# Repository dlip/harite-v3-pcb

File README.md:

# Harite v3.0 PCB

[Build Guide](/build.md)

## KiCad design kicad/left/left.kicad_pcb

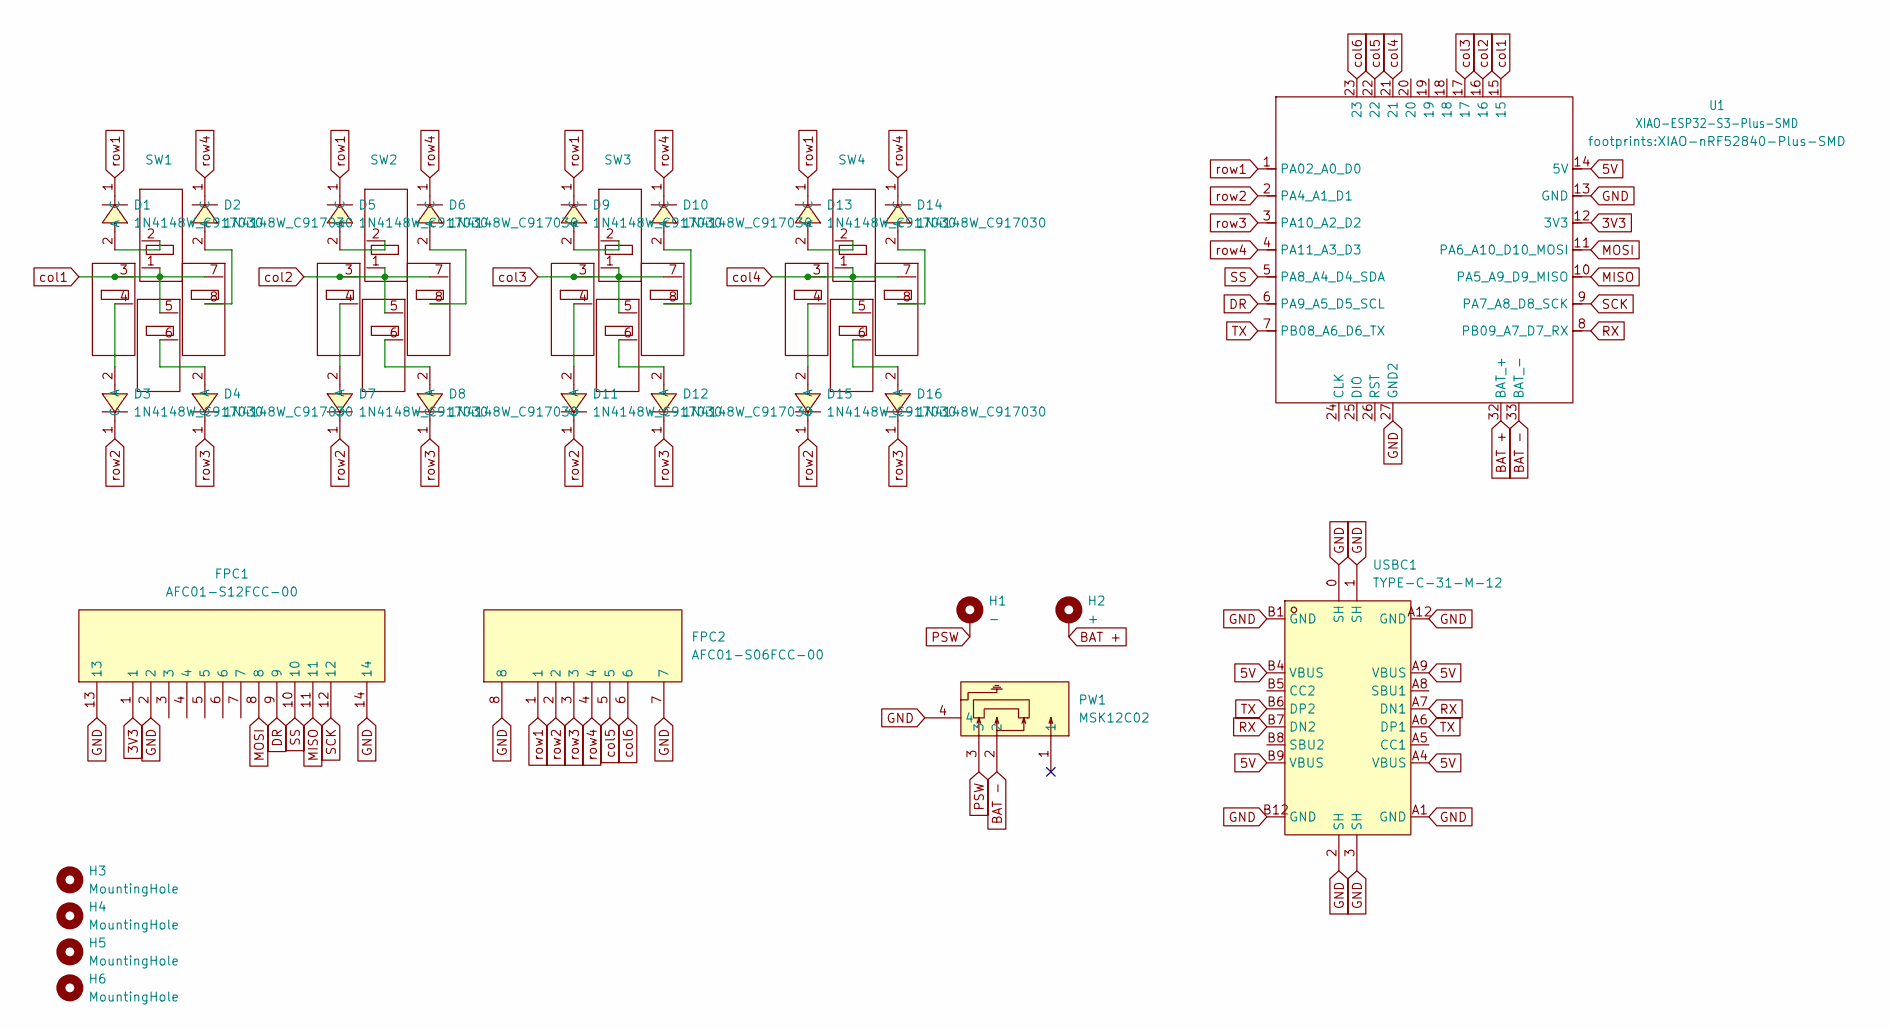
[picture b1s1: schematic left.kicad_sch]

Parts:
D1, D2, D3, D4, D5, D6, D7, D8, D9, D10, D11, D12, D13, D14, D15, D16: 1N4148W_C917030; SOD-123_L2.8-W1.8-LS3.7-RD-1; LCSC Part C917030
FPC1: AFC01-S12FCC-00; FPC-SMD_AFC01-S12FCC-00; LCSC Part C262268
FPC2: AFC01-S06FCC-00; FPC-SMD_AFC01-S06FCC-00; LCSC Part C262262
H1: -; BatteryPad
H2: +; BatteryPad
H3, H4, H5, H6: MountingHole; MountingHole_2.2mm_M2_Pad_Via
PW1: MSK12C02; SW-TH_MSK12C02; LCSC Part C431540
SW1, SW2, SW3, SW4: mouse-switch-cluster
U1: XIAO-ESP32-S3-Plus-SMD; XIAO-nRF52840-Plus-SMD
USBC1: TYPE-C-31-M-12; USB-C_SMD-TYPE-C-31-M-12; LCSC Part C165948

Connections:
3V3: FPC1.1, U1.12 (3V3)
5V: U1.14 (5V), USBC1.A4 (VBUS), USBC1.A9 (VBUS), USBC1.B4 (VBUS), USBC1.B9 (VBUS)
BAT +: H2.1, U1.32 (BAT_+)
BAT -: PW1.2, U1.33 (BAT_-)
DR: FPC1.9, U1.6 (PA9_A5_D5_SCL)
GND: FPC1.2, FPC1.13, FPC1.14, FPC2.7, FPC2.8, PW1.4, U1.13 (GND), U1.27 (GND2), USBC1.0 (SH), USBC1.1 (SH), USBC1.2 (SH), USBC1.3 (SH), USBC1.A1 (GND), USBC1.A12 (GND), USBC1.B1 (GND), USBC1.B12 (GND)
MISO: FPC1.11, U1.10 (PA5_A9_D9_MISO)
MOSI: FPC1.8, U1.11 (PA6_A10_D10_MOSI)
unnamed: D1.2 (A), SW1.2
unnamed: D2.2 (A), SW1.8
unnamed: D3.2 (A), SW1.4
unnamed: D4.2 (A), SW1.6
unnamed: D5.2 (A), SW2.2
unnamed: D6.2 (A), SW2.8
unnamed: D7.2 (A), SW2.4
unnamed: D8.2 (A), SW2.6
unnamed: D9.2 (A), SW3.2
unnamed: D10.2 (A), SW3.8
unnamed: D11.2 (A), SW3.4
unnamed: D12.2 (A), SW3.6
unnamed: D13.2 (A), SW4.2
unnamed: D14.2 (A), SW4.8
unnamed: D15.2 (A), SW4.4
unnamed: D16.2 (A), SW4.6
PSW: H1.1, PW1.3
RX: U1.8 (PB09_A7_D7_RX), USBC1.A7 (DN1), USBC1.B7 (DN2)
SCK: FPC1.12, U1.9 (PA7_A8_D8_SCK)
SS: FPC1.10, U1.5 (PA8_A4_D4_SDA)
TX: U1.7 (PB08_A6_D6_TX), USBC1.A6 (DP1), USBC1.B6 (DP2)
col1: SW1.1, SW1.3, SW1.5, SW1.7, U1.15
col2: SW2.1, SW2.3, SW2.5, SW2.7, U1.16
col3: SW3.1, SW3.3, SW3.5, SW3.7, U1.17
col4: SW4.1, SW4.3, SW4.5, SW4.7, U1.21
col5: FPC2.5, U1.22
col6: FPC2.6, U1.23
row1: D1.1 (C), D5.1 (C), D9.1 (C), D13.1 (C), FPC2.1, U1.1 (PA02_A0_D0)
row2: D3.1 (C), D7.1 (C), D11.1 (C), D15.1 (C), FPC2.2, U1.2 (PA4_A1_D1)
row3: D4.1 (C), D8.1 (C), D12.1 (C), D16.1 (C), FPC2.3, U1.3 (PA10_A2_D2)
row4: D2.1 (C), D6.1 (C), D10.1 (C), D14.1 (C), FPC2.4, U1.4 (PA11_A3_D3)

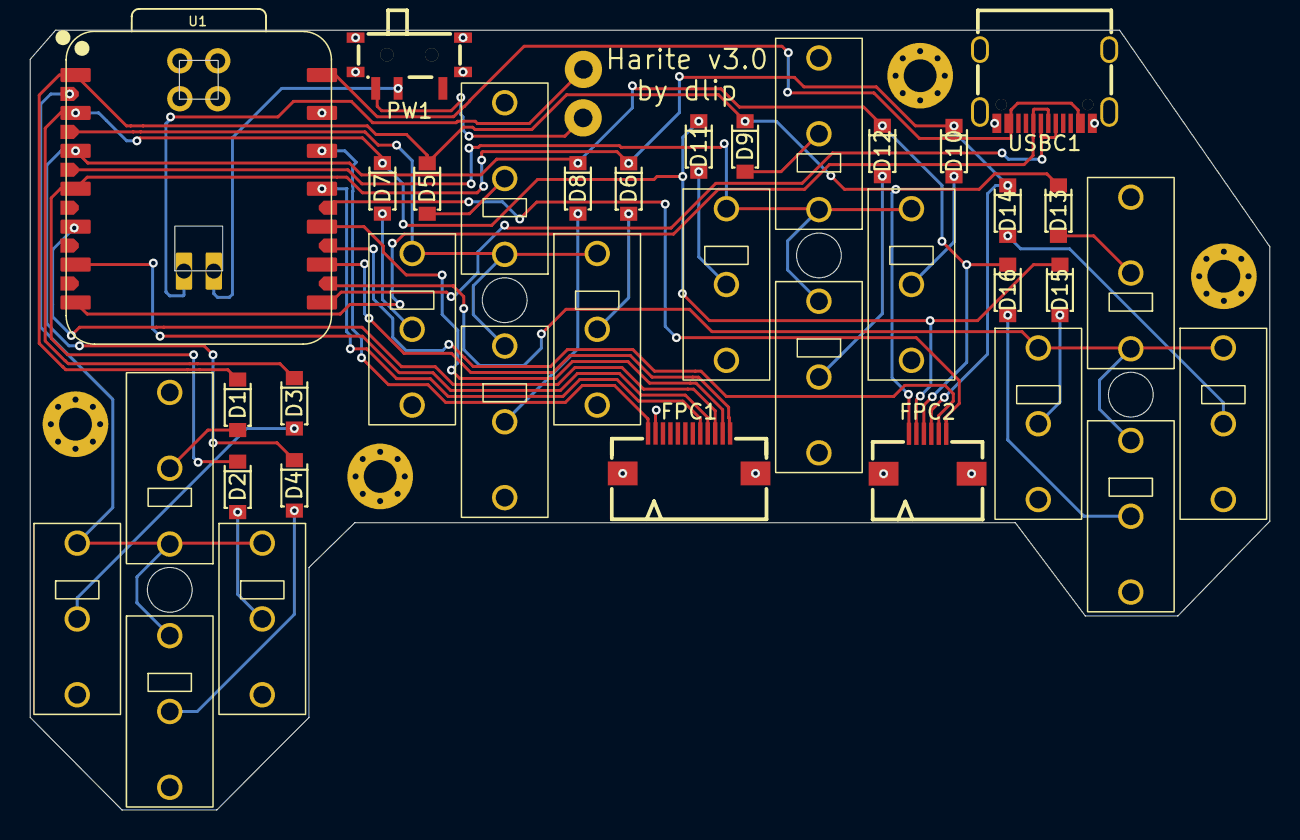
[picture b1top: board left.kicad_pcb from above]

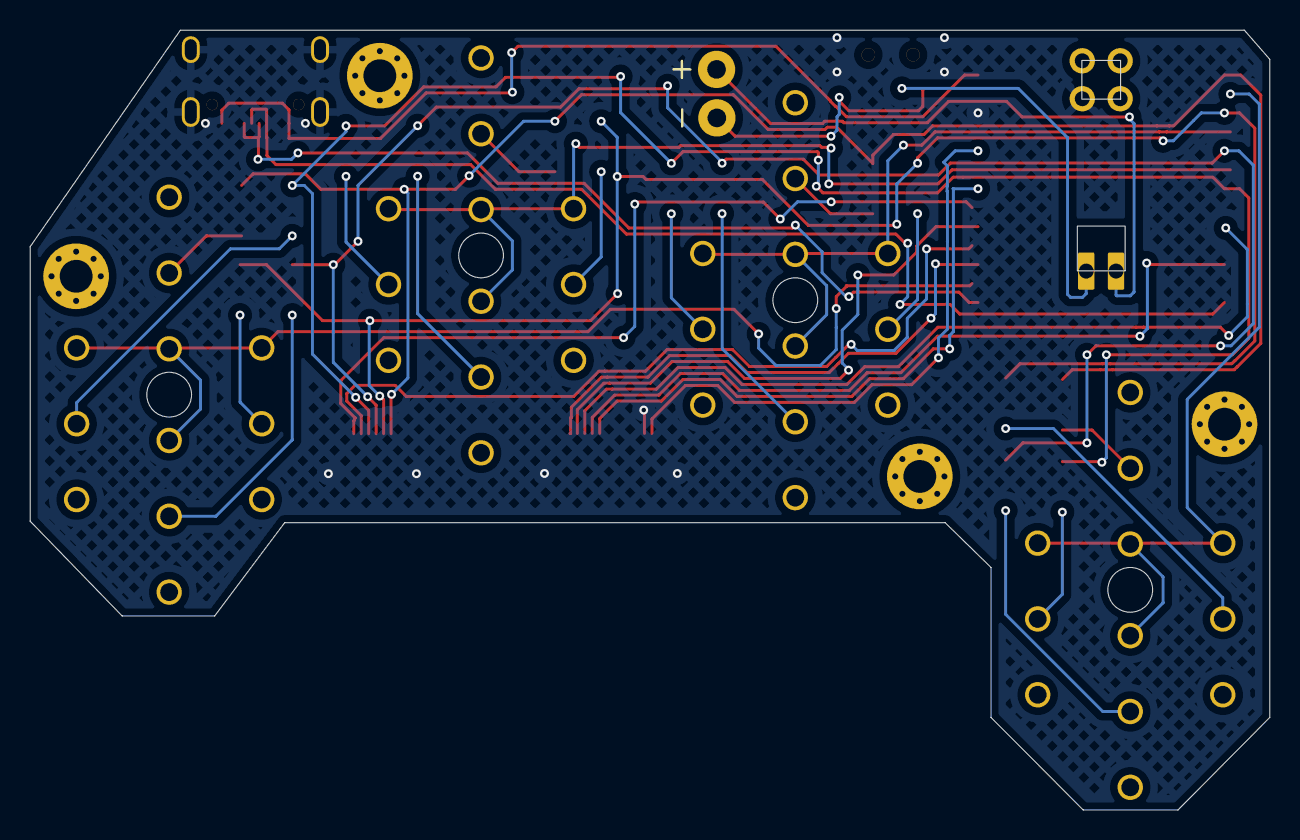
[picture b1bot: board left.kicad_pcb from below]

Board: 2 copper layers, 83.1 x 52.3 mm, 31 parts (2 on the bottom side), 39 nets.

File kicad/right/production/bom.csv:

Designator,Footprint,Quantity,Value,LCSC Part #
"D1, D10, D11, D12, D13, D14, D15, D16, D2, D3, D4, D5, D6, D7, D8, D9",SOD-123_L2.8-W1.8-LS3.7-RD-1,16,1N4148W_C917030,C917030
FPC1,FPC-SMD_AFC01-S12FCC-00,1,AFC01-S12FCC-00,C262268
FPC2,FPC-SMD_AFC01-S06FCC-00,1,AFC01-S06FCC-00,C262262
PW1,SW-TH_MSK12C02,1,MSK12C02,C431540
"SW1, SW2, SW3, SW4",mouse-switch-cluster,4,~,
U1,XIAO-nRF52840-Plus-SMD,1,XIAO-ESP32-S3-Plus-SMD,
USBC1,USB-C_SMD-TYPE-C-31-M-12,1,TYPE-C-31-M-12,C165948

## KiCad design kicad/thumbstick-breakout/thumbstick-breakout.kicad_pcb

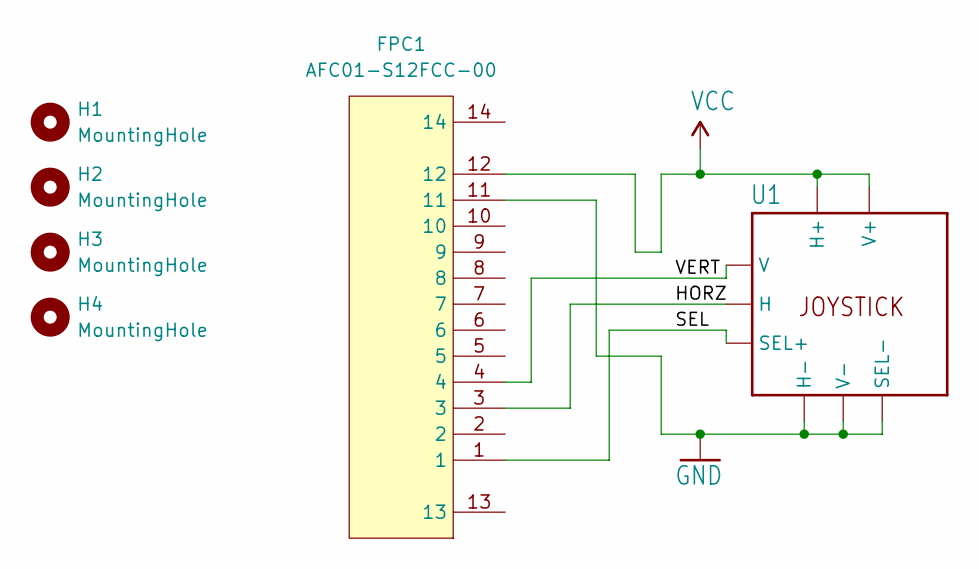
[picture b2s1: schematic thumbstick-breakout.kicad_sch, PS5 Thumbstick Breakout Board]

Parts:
FPC1: AFC01-S12FCC-00; FPC-SMD_AFC01-S12FCC-00; LCSC Part C262268
H1, H2, H3, H4: MountingHole; MountingHole_2.2mm_M2_Pad_Via
U1: Joystick

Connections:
/HORZ: FPC1.3, U1.2 (H)
/SEL: FPC1.1, U1.a (SEL+)
/VERT: FPC1.4, U1.2' (V)
GND: FPC1.11, U1.1 (H-), U1.1' (V-), U1.c (SEL-)
VCC: FPC1.12, U1.3 (H+), U1.3' (V+)

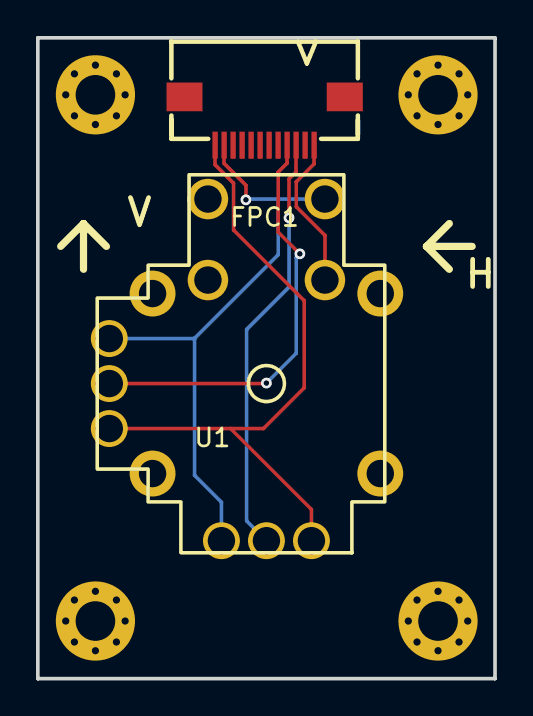
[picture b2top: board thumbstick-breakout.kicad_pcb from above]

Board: 2 copper layers, 25.4 x 35.6 mm, 6 parts (0 on the bottom side), 5 nets.

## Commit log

2025-07-23 Add Harite v3.0 PCB
2025-07-23 Add readme
2025-08-21 Fix FFC cable type

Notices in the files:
kicad/thumbstick-breakout/thumbstick-breakout.kicad_pcb:
https://creativecommons.org/licenses/by-sa/4.0
This hardware is licensed under Creative Commons ShareAlike 4.0 International
